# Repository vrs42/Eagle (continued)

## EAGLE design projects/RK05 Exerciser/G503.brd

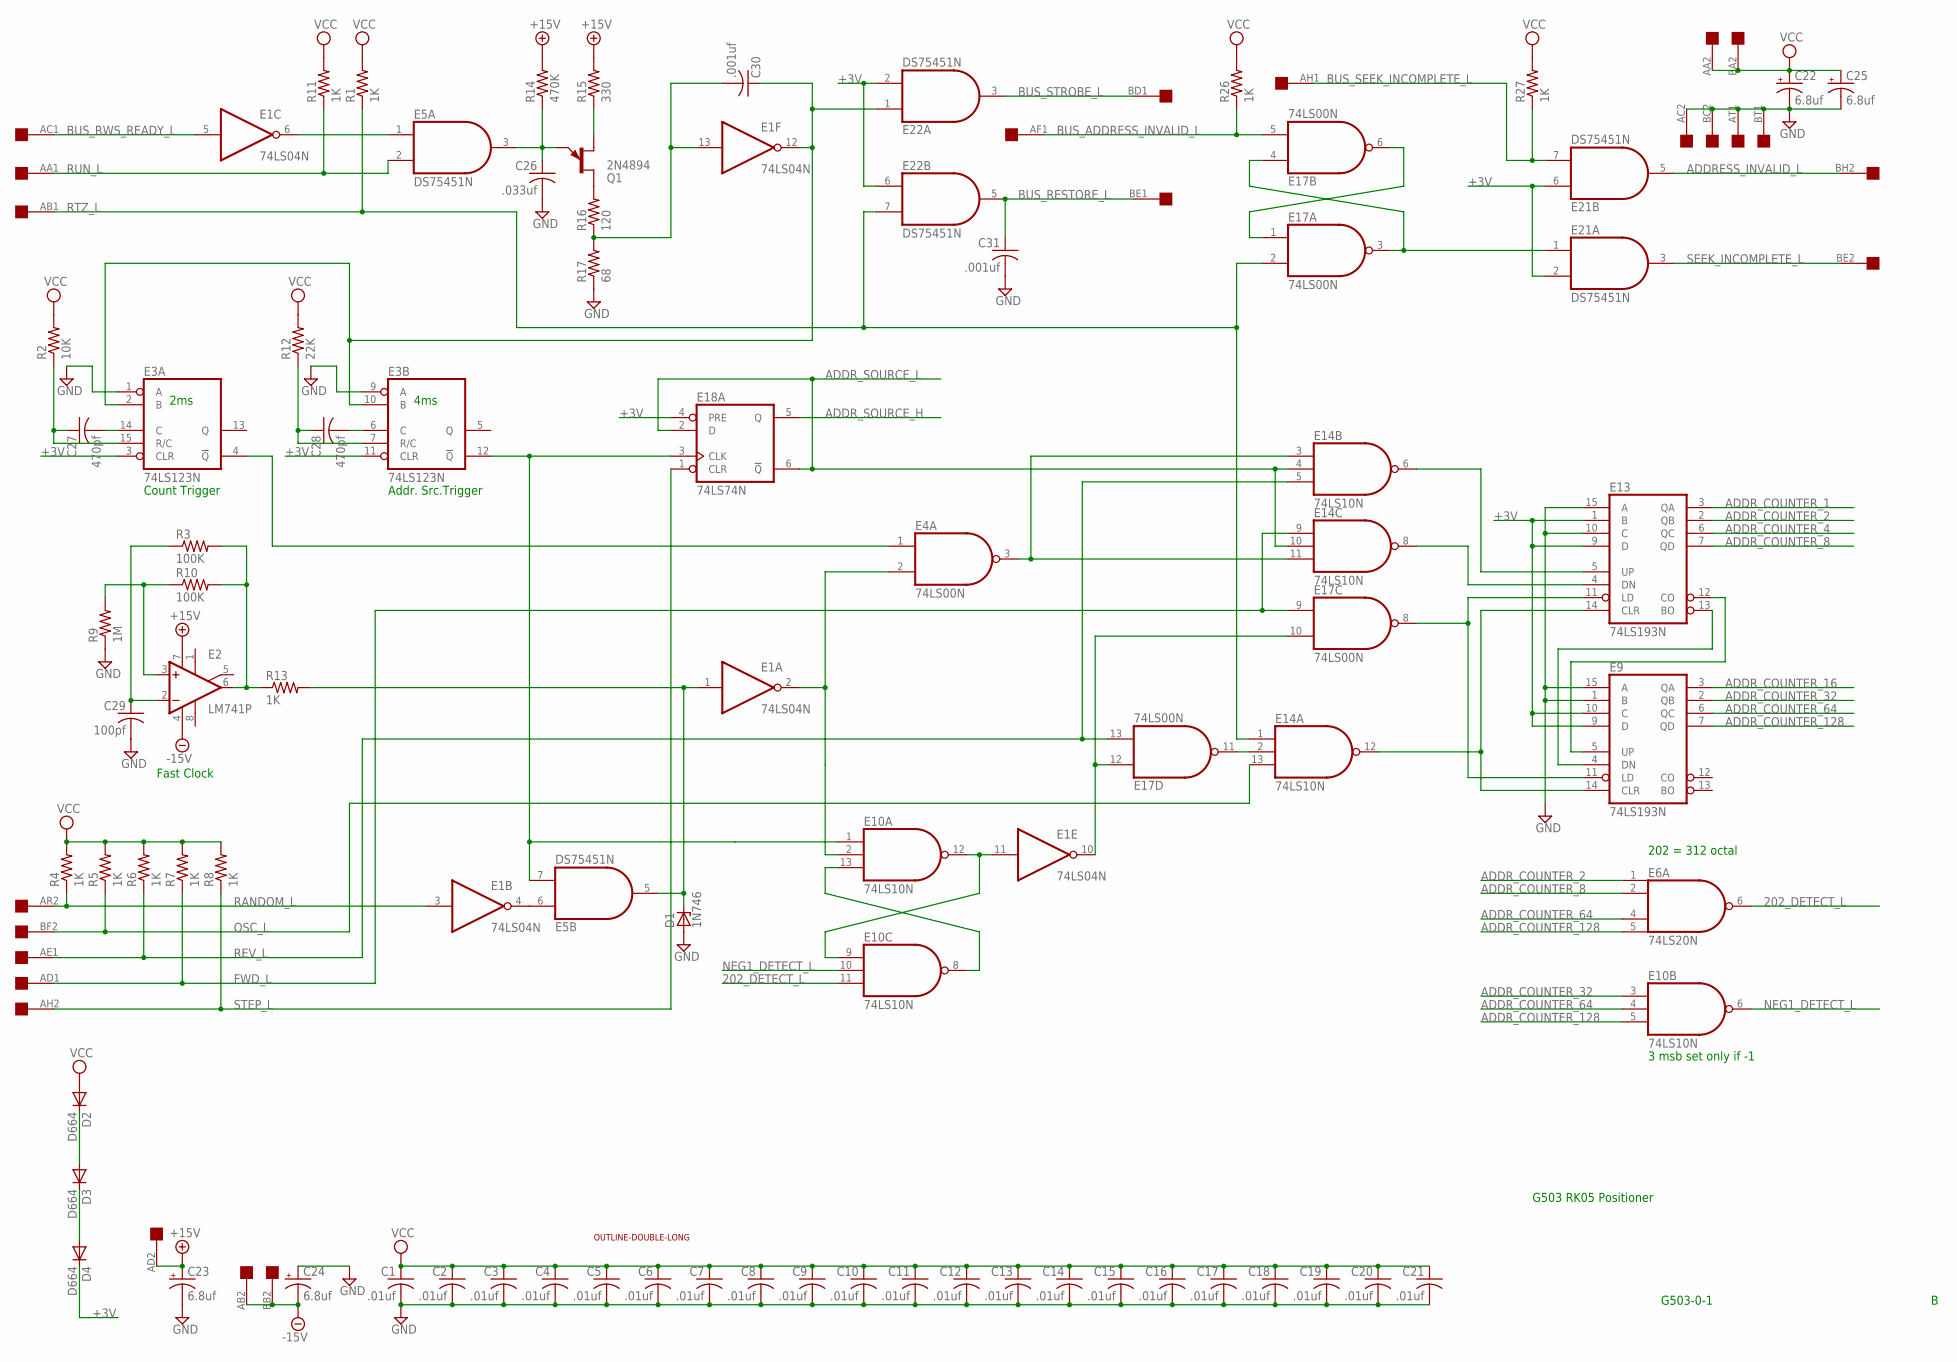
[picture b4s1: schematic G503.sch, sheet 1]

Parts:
AB03: DOUBLE; EDGE-CON4
C1, C2, C3, C4, C5, C6, C7, C8, C9, C10, C11, C12, C13, C14, C15, C16, C17, C18, C19, C20, C21: .01uf; C075-032X103
C22, C23, C24, C25: 6.8uf; E25-9
C26: .033uf; C075-032X103
C27, C28: 470pf; C075-032X103
C29: 100pf; C075-032X103
C30, C31: .001uf; C075-032X103
D1: 1N746; DO35Z10
D2, D3, D4: D664; DO35-10
E1: 74LS04N; DIL14
E2: LM741P; DIL08
E3: 74LS123N; DIL16
E4, E17: 74LS00N; DIL14
E5, E21, E22: DS75451N; DIL08
E6: 74LS20N; DIL14
E9, E13: 74LS193N; DIL16
E10, E14: 74LS10N; DIL14
E18: 74LS74N; DIL14
Q1: 2N4894; TO92E
R1, R4, R5, R6, R7, R8, R11, R13, R26, R27: 1K; 0207/10
R2: 10K; 0207/10
R3, R10: 100K; 0207/10
R9: 1M; 0207/10
R12: 22K; 0207/10
R14: 470K; 0207/10
R15: 330; 0207/10
R16: 120; 0207/10
R17: 68; 0207/10
U$1: OUTLINE-DOUBLE-LONG; DOUBLE-LONG

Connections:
202_DETECT_L: E6.6 (O), E10.11 (I2)
+3V: D4.C, E3.3 (CLR), E3.11 (CLR), E9.9 (D), E9.10 (C), E13.1 (B), E13.9 (D), E18.4 (PRE), E21.2 (I1), E21.6 (I0), E22.2 (I1), E22.6 (I0)
+15V: AB03.AD2, C23.+, E2.7 (V+), R14.2, R15.2
-15V: AB03.AB2, AB03.BB2, C24.-, E2.4 (V-)
ADDRESS_INVALID_L: AB03.BH2, E21.5 (O)
ADDR_COUNTER_1: E13.3 (QA); also elsewhere on the board
ADDR_COUNTER_2: E6.1 (I0), E13.2 (QB); also elsewhere on the board
ADDR_COUNTER_4: E13.6 (QC); also elsewhere on the board
ADDR_COUNTER_8: E6.2 (I1), E13.7 (QD); also elsewhere on the board
ADDR_COUNTER_16: E9.3 (QA); also elsewhere on the board
ADDR_COUNTER_32: E9.2 (QB), E10.3 (I0); also elsewhere on the board
ADDR_COUNTER_64: E6.4 (I2), E9.6 (QC), E10.4 (I1); also elsewhere on the board
ADDR_COUNTER_128: E6.5 (I3), E9.7 (QD), E10.5 (I2); also elsewhere on the board
ADDR_SOURCE_H: E18.5 (Q); also elsewhere on the board
ADDR_SOURCE_L: E14.4 (I1), E14.10 (I1), E18.2 (D), E18.6 (!Q); also elsewhere on the board
BUS_ADDRESS_INVALID_L: AB03.AF1, E17.5 (I1), R26.1
BUS_RESTORE_L: AB03.BE1, C31.1, E22.5 (O)
BUS_RWS_READY_L: AB03.AC1, E1.5 (I)
BUS_SEEK_INCOMPLETE_L: AB03.AH1, E21.7 (I1), R27.1
BUS_STROBE_L: AB03.BD1, E22.3 (O)
FWD_L: AB03.AD1, E14.9 (I0), E17.9 (I0), R7.1
GND: AB03.AC2, AB03.AT1, AB03.BC2, AB03.BT1, C1.2, C2.2, C3.2, C4.2, C5.2, C6.2, C7.2, C8.2, C9.2, C10.2, C11.2, C12.2, C13.2, C14.2, C15.2, C16.2, C17.2, C18.2, C19.2, C20.2, C21.2, C22.-, C23.-, C24.+, C25.-, C26.2, C29.2, C31.2, D1.A, E1.7 (GND), E3.1 (A), E3.8 (GND), E3.9 (A), E4.7 (GND), E5.4 (GND), E6.7 (GND), E9.1 (B), E9.8 (GND), E9.15 (A), E10.7 (GND), E13.8 (GND), E13.10 (C), E13.15 (A), E14.7 (GND), E17.7 (GND), E18.7 (GND), E21.4 (GND), E22.4 (GND), R9.1, R17.1; also elsewhere on the board
unnamed: E1.6 (O), E5.1 (I0)
unnamed: C26.1, E5.3 (O), Q1.E, R14.1
unnamed: Q1.B1, R15.1
unnamed: Q1.B2, R16.2
unnamed: C30.2, E1.13 (I), R16.1, R17.2
unnamed: C30.1, E1.12 (O), E3.2 (B), E3.10 (B), E22.1 (I0)
unnamed: E17.1 (I0), E17.6 (O)
unnamed: E17.3 (O), E17.4 (I0), E21.1 (I0)
unnamed: C27.1, E3.15 (R/C), R2.1
unnamed: C27.2, E3.14 (C)
unnamed: C28.1, E3.7 (R/C), R12.1
unnamed: C28.2, E3.6 (C)
unnamed: E13.5 (UP), E14.6 (O)
unnamed: E9.4 (DN), E13.13 (BO)
unnamed: E9.5 (UP), E13.12 (CO)
unnamed: E13.4 (DN), E14.8 (O)
unnamed: E9.11 (LD), E13.11 (LD), E17.8 (O)
unnamed: E9.14 (CLR), E13.14 (CLR), E14.12 (O)
unnamed: C29.1, E2.2 (-IN), R3.1
unnamed: E2.6 (OUT), R3.2, R10.2, R13.1
unnamed: E2.3 (+IN), R9.2, R10.1
unnamed: D1.C, E1.1 (I), E5.5 (O), R13.2
unnamed: E1.2 (O), E4.2 (I1), E10.2 (I1)
unnamed: E3.4 (!Q), E4.1 (I0)
unnamed: D2.C, D3.A
unnamed: D3.C, D4.A
unnamed: E1.4 (O), E5.6 (I0)
unnamed: E10.8 (O), E10.13 (I2)
unnamed: E3.12 (!Q), E5.7 (I1), E10.1 (I0), E18.3 (CLK)
unnamed: E4.3 (O), E14.3 (I0), E14.11 (I2)
unnamed: E1.11 (I), E10.9 (I0), E10.12 (O)
unnamed: E14.2 (I1), E17.11 (O)
unnamed: E1.10 (O), E17.10 (I1), E17.12 (I0)
NEG1_DETECT_L: E10.6 (O), E10.10 (I1)
OSC_L: AB03.BF2, E14.13 (I2), R5.1
RANDOM_L: AB03.AR2, E1.3 (I), R4.1
REV_L: AB03.AE1, E14.5 (I2), E17.13 (I1), R6.1
RTZ_L: AB03.AB1, E14.1 (I0), E17.2 (I1), E22.7 (I1), R1.1
RUN_L: AB03.AA1, E5.2 (I1), R11.1
SEEK_INCOMPLETE_L: AB03.BE2, E21.3 (O)
STEP_L: AB03.AH2, E18.1 (CLR), R8.1
VCC: AB03.AA2, AB03.BA2, C1.1, C2.1, C3.1, C4.1, C5.1, C6.1, C7.1, C8.1, C9.1, C10.1, C11.1, C12.1, C13.1, C14.1, C15.1, C16.1, C17.1, C18.1, C19.1, C20.1, C21.1, C22.+, C25.+, D2.A, E1.14 (VCC), E3.16 (VCC), E4.14 (VCC), E5.8 (VCC), E6.14 (VCC), E9.16 (VCC), E10.14 (VCC), E13.16 (VCC), E14.14 (VCC), E17.14 (VCC), E18.14 (VCC), E21.8 (VCC), E22.8 (VCC), R1.2, R2.2, R4.2, R5.2, R6.2, R7.2, R8.2, R11.2, R12.2, R26.2, R27.2; also elsewhere on the board

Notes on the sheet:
2ms
4ms
Count Trigger
Addr. Src.Trigger
202 = 312 octal
3 msb set only if -1
Fast Clock
G503 RK05 Positioner
G503-0-1

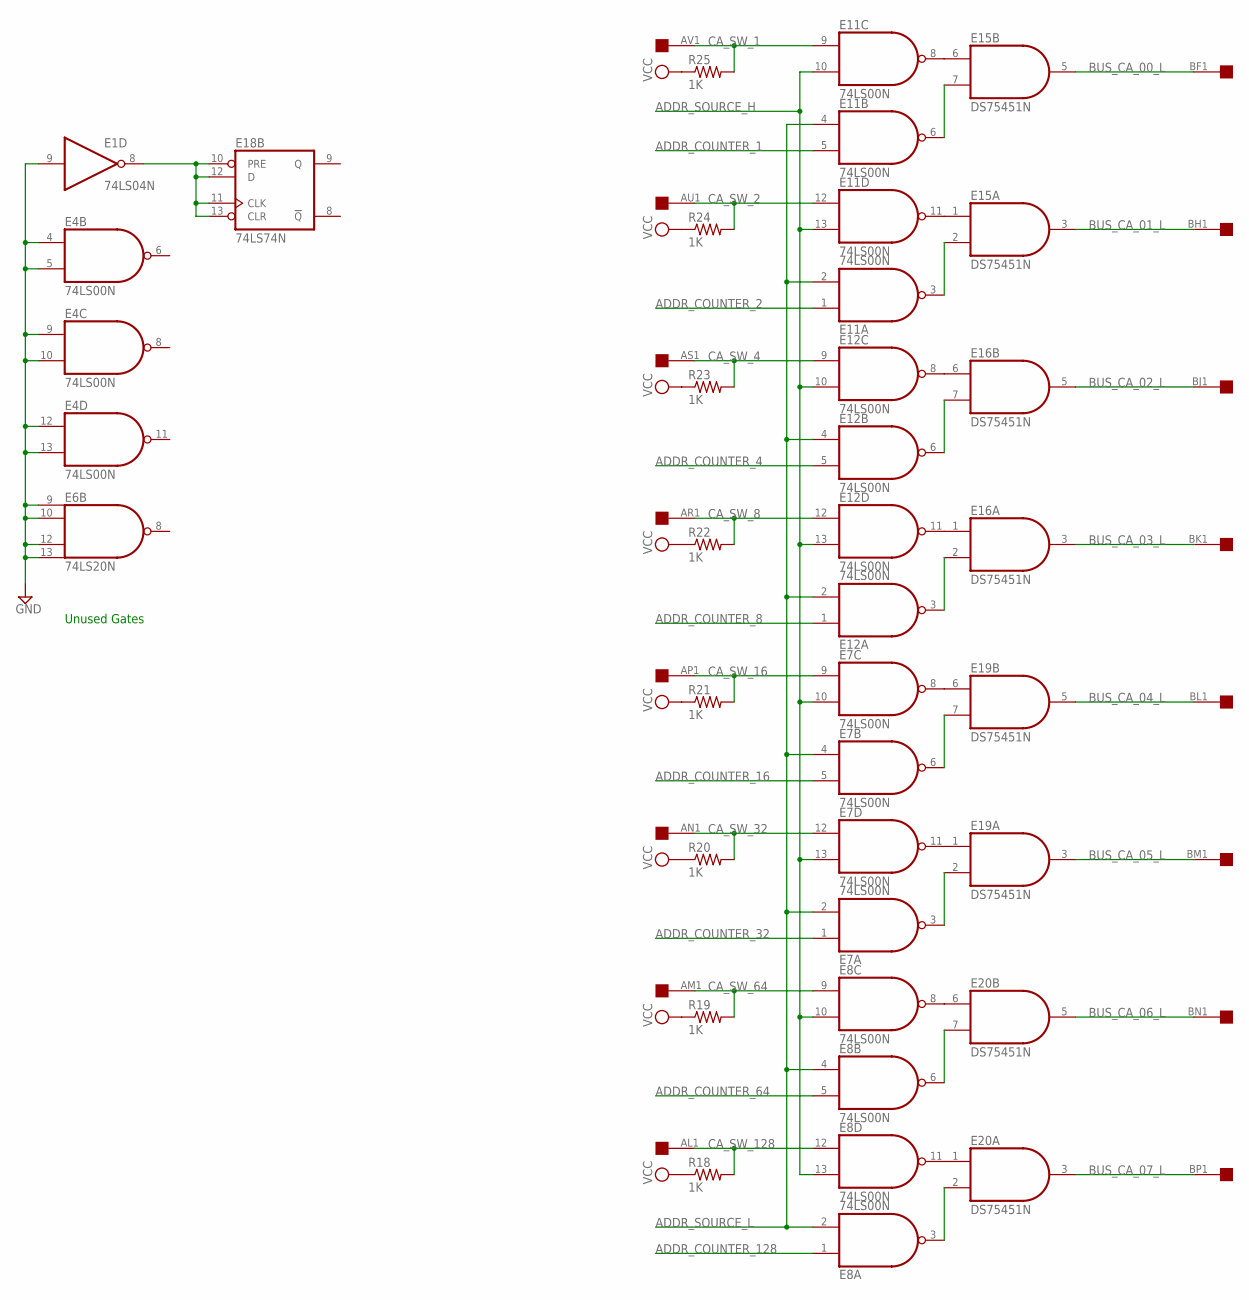
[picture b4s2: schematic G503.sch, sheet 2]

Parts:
AB03: DOUBLE; EDGE-CON4
E1: 74LS04N; DIL14
E4, E7, E8, E11, E12: 74LS00N; DIL14
E6: 74LS20N; DIL14
E15, E16, E19, E20: DS75451N; DIL08
E18: 74LS74N; DIL14
R18, R19, R20, R21, R22, R23, R24, R25: 1K; 0207/10

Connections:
ADDR_COUNTER_1: E11.5 (I1); also elsewhere on the board
ADDR_COUNTER_2: E11.1 (I0); also elsewhere on the board
ADDR_COUNTER_4: E12.5 (I1); also elsewhere on the board
ADDR_COUNTER_8: E12.1 (I0); also elsewhere on the board
ADDR_COUNTER_16: E7.5 (I1); also elsewhere on the board
ADDR_COUNTER_32: E7.1 (I0); also elsewhere on the board
ADDR_COUNTER_64: E8.5 (I1); also elsewhere on the board
ADDR_COUNTER_128: E8.1 (I0); also elsewhere on the board
ADDR_SOURCE_H: E7.10 (I1), E7.13 (I1), E8.10 (I1), E8.13 (I1), E11.10 (I1), E11.13 (I1), E12.10 (I1), E12.13 (I1); also elsewhere on the board
ADDR_SOURCE_L: E7.2 (I1), E7.4 (I0), E8.2 (I1), E8.4 (I0), E11.2 (I1), E11.4 (I0), E12.2 (I1), E12.4 (I0); also elsewhere on the board
BUS_CA_00_L: AB03.BF1, E15.5 (O)
BUS_CA_01_L: AB03.BH1, E15.3 (O)
BUS_CA_02_L: AB03.BJ1, E16.5 (O)
BUS_CA_03_L: AB03.BK1, E16.3 (O)
BUS_CA_04_L: AB03.BL1, E19.5 (O)
BUS_CA_05_L: AB03.BM1, E19.3 (O)
BUS_CA_06_L: AB03.BN1, E20.5 (O)
BUS_CA_07_L: AB03.BP1, E20.3 (O)
CA_SW_1: AB03.AV1, E11.9 (I0), R25.2
CA_SW_2: AB03.AU1, E11.12 (I0), R24.2
CA_SW_4: AB03.AS1, E12.9 (I0), R23.2
CA_SW_8: AB03.AR1, E12.12 (I0), R22.2
CA_SW_16: AB03.AP1, E7.9 (I0), R21.2
CA_SW_32: AB03.AN1, E7.12 (I0), R20.2
CA_SW_64: AB03.AM1, E8.9 (I0), R19.2
CA_SW_128: AB03.AL1, E8.12 (I0), R18.2
GND: E1.7 (GND), E1.9 (I), E4.4 (I0), E4.5 (I1), E4.7 (GND), E4.9 (I0), E4.10 (I1), E4.12 (I0), E4.13 (I1), E6.7 (GND), E6.9 (I0), E6.10 (I1), E6.12 (I2), E6.13 (I3), E7.7 (GND), E8.7 (GND), E11.7 (GND), E12.7 (GND), E15.4 (GND), E16.4 (GND), E18.7 (GND), E19.4 (GND), E20.4 (GND); also elsewhere on the board
unnamed: E11.6 (O), E15.7 (I1)
unnamed: E11.8 (O), E15.6 (I0)
unnamed: E11.3 (O), E15.2 (I1)
unnamed: E11.11 (O), E15.1 (I0)
unnamed: E12.8 (O), E16.6 (I0)
unnamed: E12.6 (O), E16.7 (I1)
unnamed: E12.11 (O), E16.1 (I0)
unnamed: E12.3 (O), E16.2 (I1)
unnamed: E7.6 (O), E19.7 (I1)
unnamed: E7.3 (O), E19.2 (I1)
unnamed: E8.6 (O), E20.7 (I1)
unnamed: E8.3 (O), E20.2 (I1)
unnamed: E8.11 (O), E20.1 (I0)
unnamed: E8.8 (O), E20.6 (I0)
unnamed: E7.11 (O), E19.1 (I0)
unnamed: E7.8 (O), E19.6 (I0)
unnamed: E1.8 (O), E18.10 (PRE), E18.11 (CLK), E18.12 (D), E18.13 (CLR)
VCC: E1.14 (VCC), E4.14 (VCC), E6.14 (VCC), E7.14 (VCC), E8.14 (VCC), E11.14 (VCC), E12.14 (VCC), E15.8 (VCC), E16.8 (VCC), E18.14 (VCC), E19.8 (VCC), E20.8 (VCC), R18.1, R19.1, R20.1, R21.1, R22.1, R23.1, R24.1, R25.1; also elsewhere on the board

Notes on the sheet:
Unused Gates

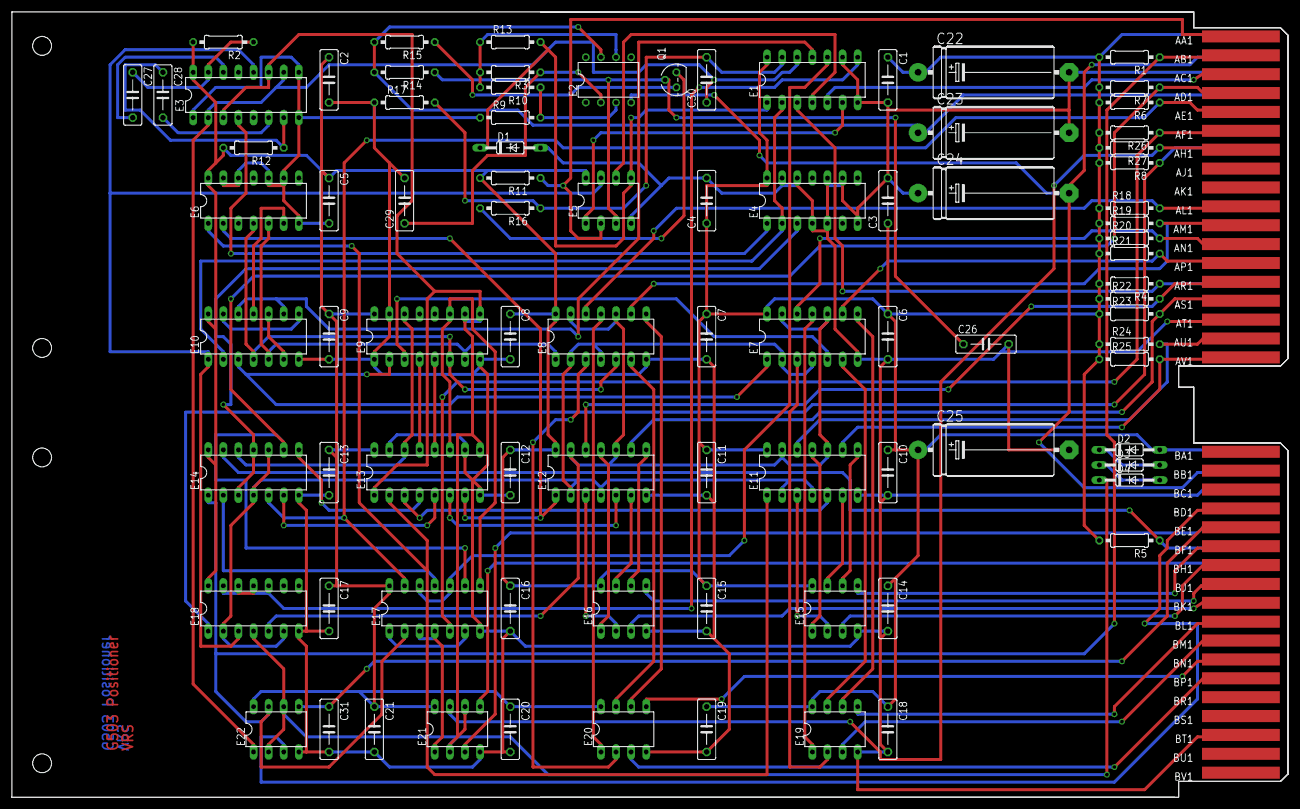
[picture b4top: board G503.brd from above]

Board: 2 copper layers, 214.6 x 132.1 mm, 87 parts (0 on the bottom side), 97 nets.

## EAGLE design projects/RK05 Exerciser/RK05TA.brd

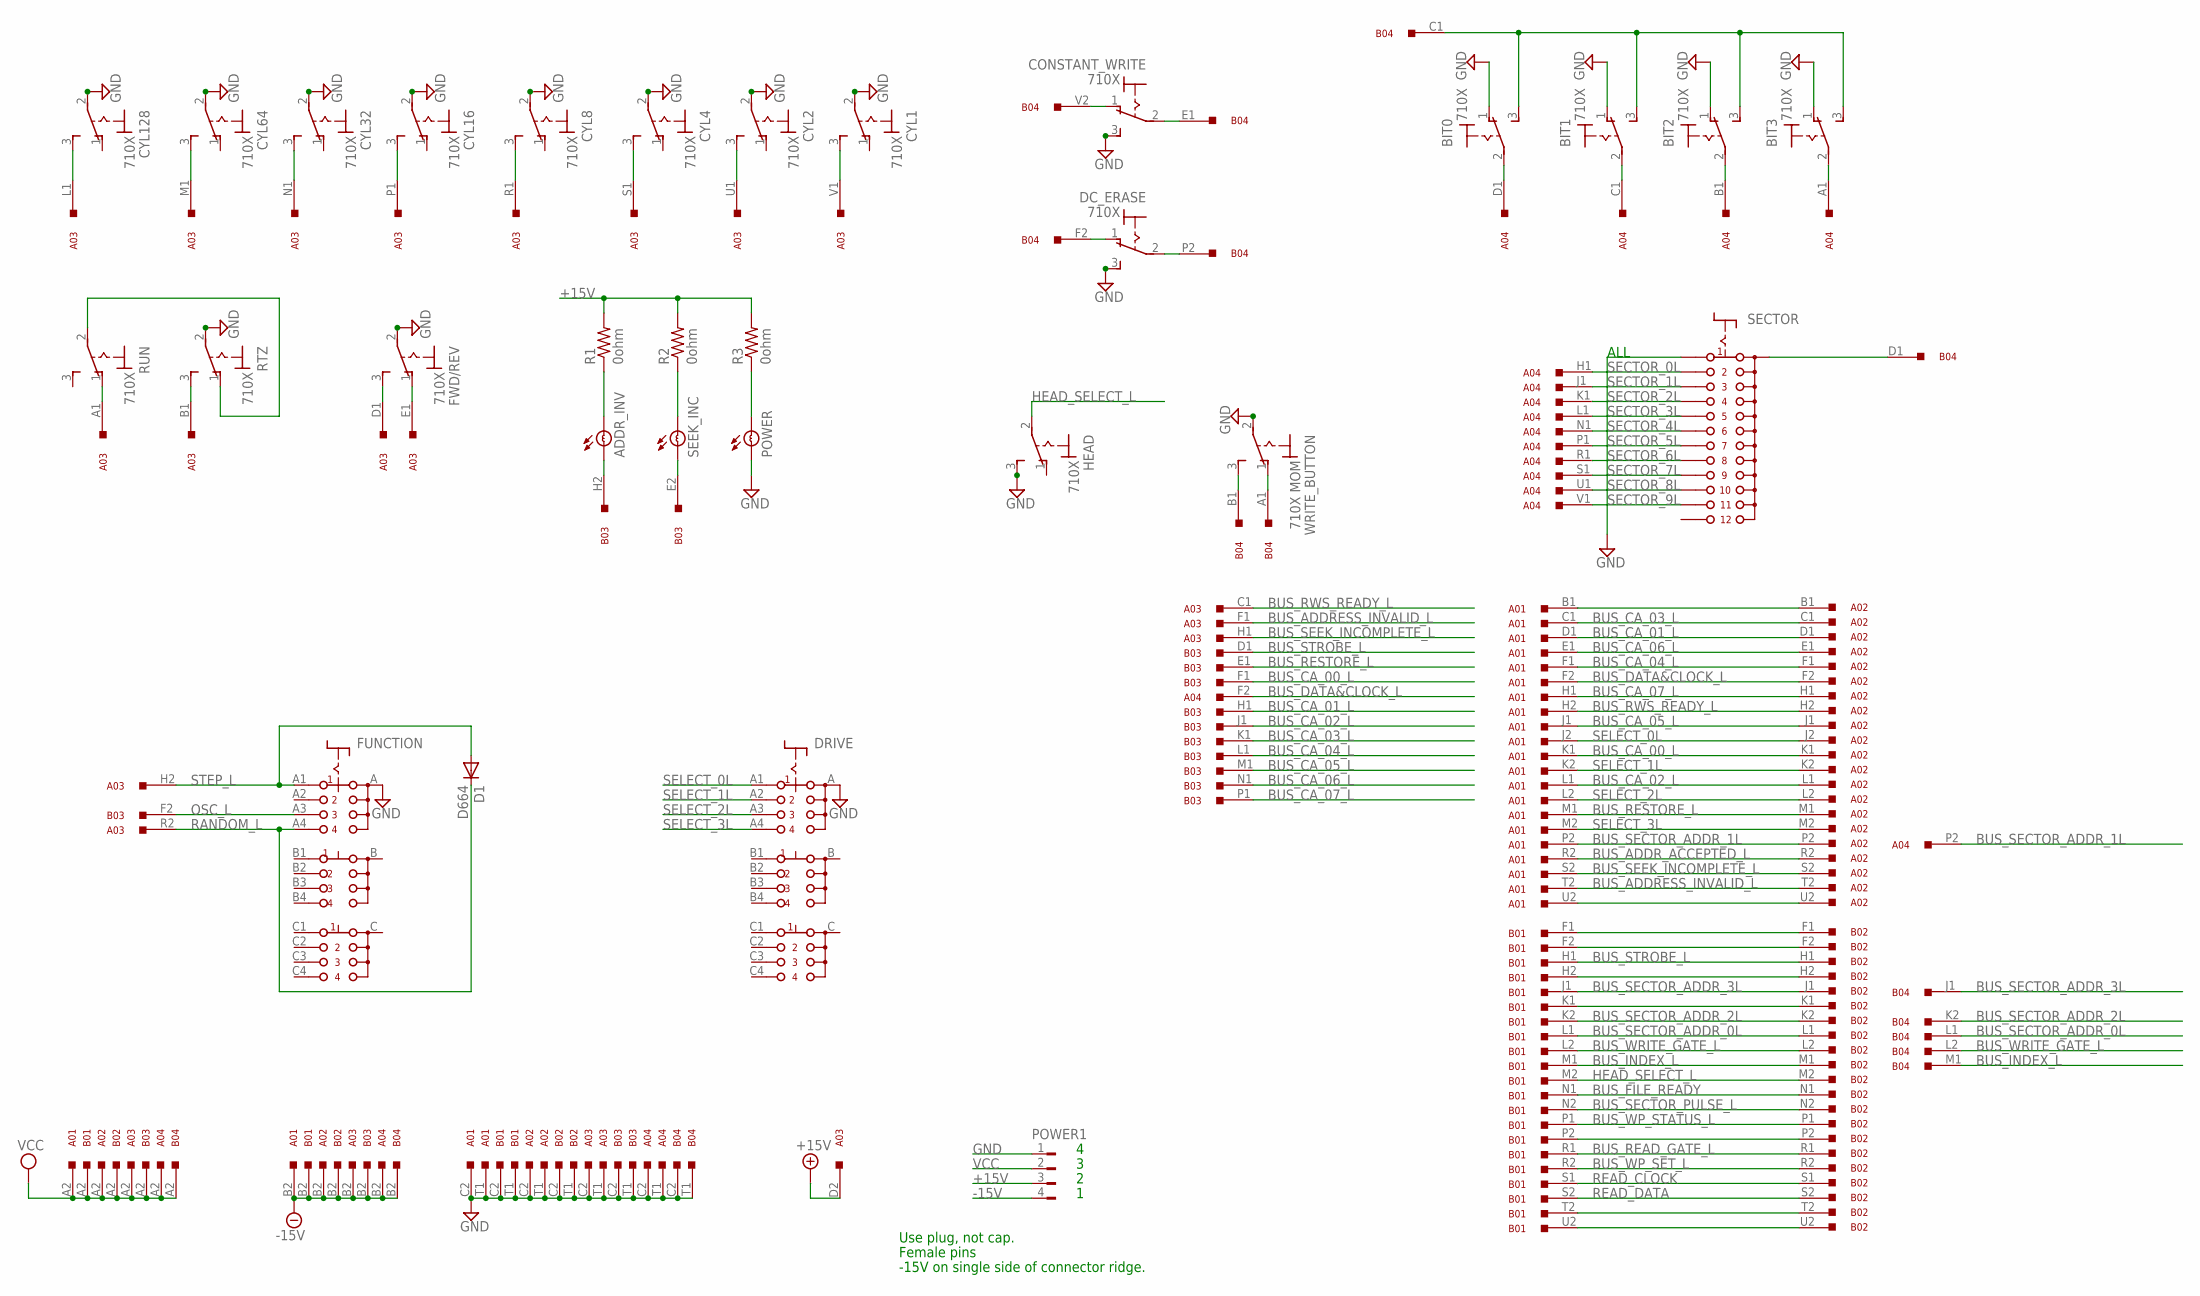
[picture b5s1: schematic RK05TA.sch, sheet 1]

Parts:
A01: BC11A; H807
A02: M930; H807
A03: G503; H807
A04: G502; H807
ADDR_INV: BULB
B01: BC11A; H807
B02: M930; H807
B03: G503; H807
B04: G502; H807
BIT0, BIT1, BIT2, BIT3: 710X; 7109MD9V3
CONSTANT_WRITE: 710X; 7109MD9V3
CYL1, CYL2, CYL4, CYL8, CYL16, CYL32, CYL64, CYL128: 710X; 7109MD9V3
D1: D664; DO35-10
DC_ERASE: 710X; 7109MD9V3
DRIVE: CK103X04
FUNCTION: CK103X04
FWD/REV: 710X; 7109MD9V3
HEAD: 710X; 7109MD9V3
POWER: BULB
POWER1: FLOPPY-4
R1, R2, R3: 0ohm; 0207/10
RTZ: 710X; 7109MD9V3
RUN: 710X; 7109MD9V3
SECTOR: CK101X12
SEEK_INC: BULB
WRITE_BUTTON: 710X MOM; 7109MD9V3

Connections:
+3VA: B04.F2, DC_ERASE.1 (O); also elsewhere on the board
+3VC: B04.V2, CONSTANT_WRITE.1 (O); also elsewhere on the board
+15V: A03.D2, POWER1.3, R1.2, R2.2, R3.2; also elsewhere on the board
-15V: A01.B2, A02.B2, A03.B2, A04.B2, B01.B2, B02.B2, B03.B2, B04.B2, POWER1.4; also elsewhere on the board
ADDRESS_INVALID_L: ADDR_INV.B, B03.H2; also elsewhere on the board
BIT_0L: A04.D1, BIT0.2; also elsewhere on the board
BIT_1L: A04.C1, BIT1.2; also elsewhere on the board
BIT_2L: A04.B1, BIT2.2; also elsewhere on the board
BIT_3L: A04.A1, BIT3.2; also elsewhere on the board
BUS_ADDRESS_INVALID_L: A01.T2, A02.T2, A03.F1
BUS_ADDR_ACCEPTED_L: A01.R2, A02.R2
BUS_CA_00_L: A01.K1, A02.K1, B03.F1
BUS_CA_01_L: A01.D1, A02.D1, B03.H1
BUS_CA_02_L: A01.L1, A02.L1, B03.J1
BUS_CA_03_L: A01.C1, A02.C1, B03.K1
BUS_CA_04_L: A01.F1, A02.F1, B03.L1
BUS_CA_05_L: A01.J1, A02.J1, B03.M1
BUS_CA_06_L: A01.E1, A02.E1, B03.N1
BUS_CA_07_L: A01.H1, A02.H1, B03.P1
BUS_DATA&CLOCK_L: A01.F2, A02.F2, A04.F2
BUS_FILE_READY: B01.N1, B02.N1
BUS_INDEX_L: B01.M1, B02.M1, B04.M1
BUS_READ_GATE_L: B01.R1, B02.R1
BUS_RESTORE_L: A01.M1, A02.M1, B03.E1
BUS_RWS_READY_L: A01.H2, A02.H2, A03.C1
BUS_SECTOR_ADDR_0L: B01.L1, B02.L1, B04.L1
BUS_SECTOR_ADDR_1L: A01.P2, A02.P2, A04.P2
BUS_SECTOR_ADDR_2L: B01.K2, B02.K2, B04.K2
BUS_SECTOR_ADDR_3L: B01.J1, B02.J1, B04.J1
BUS_SECTOR_PULSE_L: B01.N2, B02.N2
BUS_SEEK_INCOMPLETE_L: A01.S2, A02.S2, A03.H1
BUS_STROBE_L: B01.H1, B02.H1, B03.D1
BUS_WP_SET_L: B01.R2, B02.R2
BUS_WP_STATUS_L: B01.P1, B02.P1
BUS_WRITE_GATE_L: B01.L2, B02.L2, B04.L2
CA_SW_1: A03.V1, CYL1.3 (S); also elsewhere on the board
CA_SW_2: A03.U1, CYL2.3 (S); also elsewhere on the board
CA_SW_4: A03.S1, CYL4.3 (S); also elsewhere on the board
CA_SW_8: A03.R1, CYL8.3 (S); also elsewhere on the board
CA_SW_16: A03.P1, CYL16.3 (S); also elsewhere on the board
CA_SW_32: A03.N1, CYL32.3 (S); also elsewhere on the board
CA_SW_64: A03.M1, CYL64.3 (S); also elsewhere on the board
CA_SW_128: A03.L1, CYL128.3 (S); also elsewhere on the board
CONSTANT_WRITE_L: B04.E1, CONSTANT_WRITE.2; also elsewhere on the board
DATA_BITS: B04.C1, BIT0.3 (S), BIT1.3 (S), BIT2.3 (S), BIT3.3 (S); also elsewhere on the board
DC_ERASE: B04.P2, DC_ERASE.2; also elsewhere on the board
FWD_L: A03.D1, FWD/REV.3 (S); also elsewhere on the board
GND: A01.C2, A01.T1, A02.C2, A02.T1, A03.C2, A03.T1, A04.C2, A04.T1, B01.C2, B01.T1, B02.C2, B02.T1, B03.C2, B03.T1, B04.C2, B04.T1, BIT0.1 (O), BIT0.NC@1 (GND), BIT0.NC@2 (GND), BIT0.NC@3 (GND), BIT0.NC@4 (GND), BIT0.NC@5 (GND), BIT0.NC@6 (GND), BIT0.NC@7 (GND), BIT0.NC@8 (GND), BIT1.1 (O), BIT1.NC@1 (GND), BIT1.NC@2 (GND), BIT1.NC@3 (GND), BIT1.NC@4 (GND), BIT1.NC@5 (GND), BIT1.NC@6 (GND), BIT1.NC@7 (GND), BIT1.NC@8 (GND), BIT2.1 (O), BIT2.NC@1 (GND), BIT2.NC@2 (GND), BIT2.NC@3 (GND), BIT2.NC@4 (GND), BIT2.NC@5 (GND), BIT2.NC@6 (GND), BIT2.NC@7 (GND), BIT2.NC@8 (GND), BIT3.1 (O), BIT3.NC@1 (GND), BIT3.NC@2 (GND), BIT3.NC@3 (GND), BIT3.NC@4 (GND), BIT3.NC@5 (GND), BIT3.NC@6 (GND), BIT3.NC@7 (GND), BIT3.NC@8 (GND), CONSTANT_WRITE.3 (S), CONSTANT_WRITE.NC@1 (GND), CONSTANT_WRITE.NC@2 (GND), CONSTANT_WRITE.NC@3 (GND), CONSTANT_WRITE.NC@4 (GND), CONSTANT_WRITE.NC@5 (GND), CONSTANT_WRITE.NC@6 (GND), CONSTANT_WRITE.NC@7 (GND), CONSTANT_WRITE.NC@8 (GND), CYL1.2, CYL1.NC@1 (GND), CYL1.NC@2 (GND), CYL1.NC@3 (GND), CYL1.NC@4 (GND), CYL1.NC@5 (GND), CYL1.NC@6 (GND), CYL1.NC@7 (GND), CYL1.NC@8 (GND), CYL2.2, CYL2.NC@1 (GND), CYL2.NC@2 (GND), CYL2.NC@3 (GND), CYL2.NC@4 (GND), CYL2.NC@5 (GND), CYL2.NC@6 (GND), CYL2.NC@7 (GND), CYL2.NC@8 (GND), CYL4.2, CYL4.NC@1 (GND), CYL4.NC@2 (GND), CYL4.NC@3 (GND), CYL4.NC@4 (GND), CYL4.NC@5 (GND), CYL4.NC@6 (GND), CYL4.NC@7 (GND), CYL4.NC@8 (GND), CYL8.2, CYL8.NC@1 (GND), CYL8.NC@2 (GND), CYL8.NC@3 (GND), CYL8.NC@4 (GND), CYL8.NC@5 (GND), CYL8.NC@6 (GND), CYL8.NC@7 (GND), CYL8.NC@8 (GND), CYL16.2, CYL16.NC@1 (GND), CYL16.NC@2 (GND), CYL16.NC@3 (GND), CYL16.NC@4 (GND), CYL16.NC@5 (GND), CYL16.NC@6 (GND), CYL16.NC@7 (GND), CYL16.NC@8 (GND), CYL32.2, CYL32.NC@1 (GND), CYL32.NC@2 (GND), CYL32.NC@3 (GND), CYL32.NC@4 (GND), CYL32.NC@5 (GND), CYL32.NC@6 (GND), CYL32.NC@7 (GND), CYL32.NC@8 (GND), CYL64.2, CYL64.NC@1 (GND), CYL64.NC@2 (GND), CYL64.NC@3 (GND), CYL64.NC@4 (GND), CYL64.NC@5 (GND), CYL64.NC@6 (GND), CYL64.NC@7 (GND), CYL64.NC@8 (GND), CYL128.2, CYL128.NC@1 (GND), CYL128.NC@2 (GND), CYL128.NC@3 (GND), CYL128.NC@4 (GND), CYL128.NC@5 (GND), CYL128.NC@6 (GND), CYL128.NC@7 (GND), CYL128.NC@8 (GND), DC_ERASE.3 (S), DC_ERASE.NC@1 (GND), DC_ERASE.NC@2 (GND), DC_ERASE.NC@3 (GND), DC_ERASE.NC@4 (GND), DC_ERASE.NC@5 (GND), DC_ERASE.NC@6 (GND), DC_ERASE.NC@7 (GND), DC_ERASE.NC@8 (GND), DRIVE.A, FUNCTION.A, FWD/REV.2, FWD/REV.NC@1 (GND), FWD/REV.NC@2 (GND), FWD/REV.NC@3 (GND), FWD/REV.NC@4 (GND), FWD/REV.NC@5 (GND), FWD/REV.NC@6 (GND), FWD/REV.NC@7 (GND), FWD/REV.NC@8 (GND), HEAD.3 (S), HEAD.NC@1 (GND), HEAD.NC@2 (GND), HEAD.NC@3 (GND), HEAD.NC@4 (GND), HEAD.NC@5 (GND), HEAD.NC@6 (GND), HEAD.NC@7 (GND), HEAD.NC@8 (GND), POWER.B, POWER1.1, RTZ.2, RTZ.NC@1 (GND), RTZ.NC@2 (GND), RTZ.NC@3 (GND), RTZ.NC@4 (GND), RTZ.NC@5 (GND), RTZ.NC@6 (GND), RTZ.NC@7 (GND), RTZ.NC@8 (GND), RUN.NC@1 (GND), RUN.NC@2 (GND), RUN.NC@3 (GND), RUN.NC@4 (GND), RUN.NC@5 (GND), RUN.NC@6 (GND), RUN.NC@7 (GND), RUN.NC@8 (GND), SECTOR.1, WRITE_BUTTON.2, WRITE_BUTTON.NC@1 (GND), WRITE_BUTTON.NC@2 (GND), WRITE_BUTTON.NC@3 (GND), WRITE_BUTTON.NC@4 (GND), WRITE_BUTTON.NC@5 (GND), WRITE_BUTTON.NC@6 (GND), WRITE_BUTTON.NC@7 (GND), WRITE_BUTTON.NC@8 (GND); also elsewhere on the board
HEAD_SELECT_L: B01.M2, B02.M2, HEAD.2; also elsewhere on the board
unnamed: RTZ.1 (O), RUN.2
unnamed: ADDR_INV.A, R1.1
unnamed: R2.1, SEEK_INC.A
unnamed: POWER.A, R3.1
unnamed: A01.U2, A02.U2
unnamed: B01.T2, B02.T2
unnamed: A01.B1, A02.B1
unnamed: B01.F1, B02.F1
unnamed: B01.F2, B02.F2
unnamed: B01.H2, B02.H2
unnamed: B01.K1, B02.K1
unnamed: B01.P2, B02.P2
unnamed: B01.U2, B02.U2
OSC_L: B03.F2, FUNCTION.A3; also elsewhere on the board
RANDOM_L: A03.R2, D1.C, FUNCTION.A4; also elsewhere on the board
READ_CLOCK: B01.S1, B02.S1
READ_DATA: B01.S2, B02.S2
REV_L: A03.E1, FWD/REV.1 (O); also elsewhere on the board
RTZ_L: A03.B1, RTZ.3 (S); also elsewhere on the board
RUN_L: A03.A1, RUN.1 (O); also elsewhere on the board
SECTOR_0L: A04.H1, SECTOR.2; also elsewhere on the board
SECTOR_1L: A04.J1, SECTOR.3; also elsewhere on the board
SECTOR_2L: A04.K1, SECTOR.4; also elsewhere on the board
SECTOR_3L: A04.L1, SECTOR.5; also elsewhere on the board
SECTOR_4L: A04.N1, SECTOR.6; also elsewhere on the board
SECTOR_5L: A04.P1, SECTOR.7; also elsewhere on the board
SECTOR_6L: A04.R1, SECTOR.8; also elsewhere on the board
SECTOR_7L: A04.S1, SECTOR.9; also elsewhere on the board
SECTOR_8L: A04.U1, SECTOR.10; also elsewhere on the board
SECTOR_9L: A04.V1, SECTOR.11; also elsewhere on the board
SECTOR_SELECT_L: B04.D1, SECTOR.A; also elsewhere on the board
SEEK_INCOMPLETE_L: B03.E2, SEEK_INC.B; also elsewhere on the board
SELECT_0L: A01.J2, A02.J2, DRIVE.A1; also elsewhere on the board
SELECT_1L: A01.K2, A02.K2, DRIVE.A2; also elsewhere on the board
SELECT_2L: A01.L2, A02.L2, DRIVE.A3; also elsewhere on the board
SELECT_3L: A01.M2, A02.M2, DRIVE.A4; also elsewhere on the board
STEP_L: A03.H2, D1.A, FUNCTION.A1; also elsewhere on the board
VCC: A01.A2, A02.A2, A03.A2, A04.A2, B01.A2, B02.A2, B03.A2, B04.A2, POWER1.2; also elsewhere on the board
WRITE_H: B04.A1, WRITE_BUTTON.1 (O); also elsewhere on the board
WRITE_L: B04.B1, WRITE_BUTTON.3 (S); also elsewhere on the board

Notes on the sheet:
ALL
Use plug, not cap.
Female pins
-15V on single side of connector ridge.

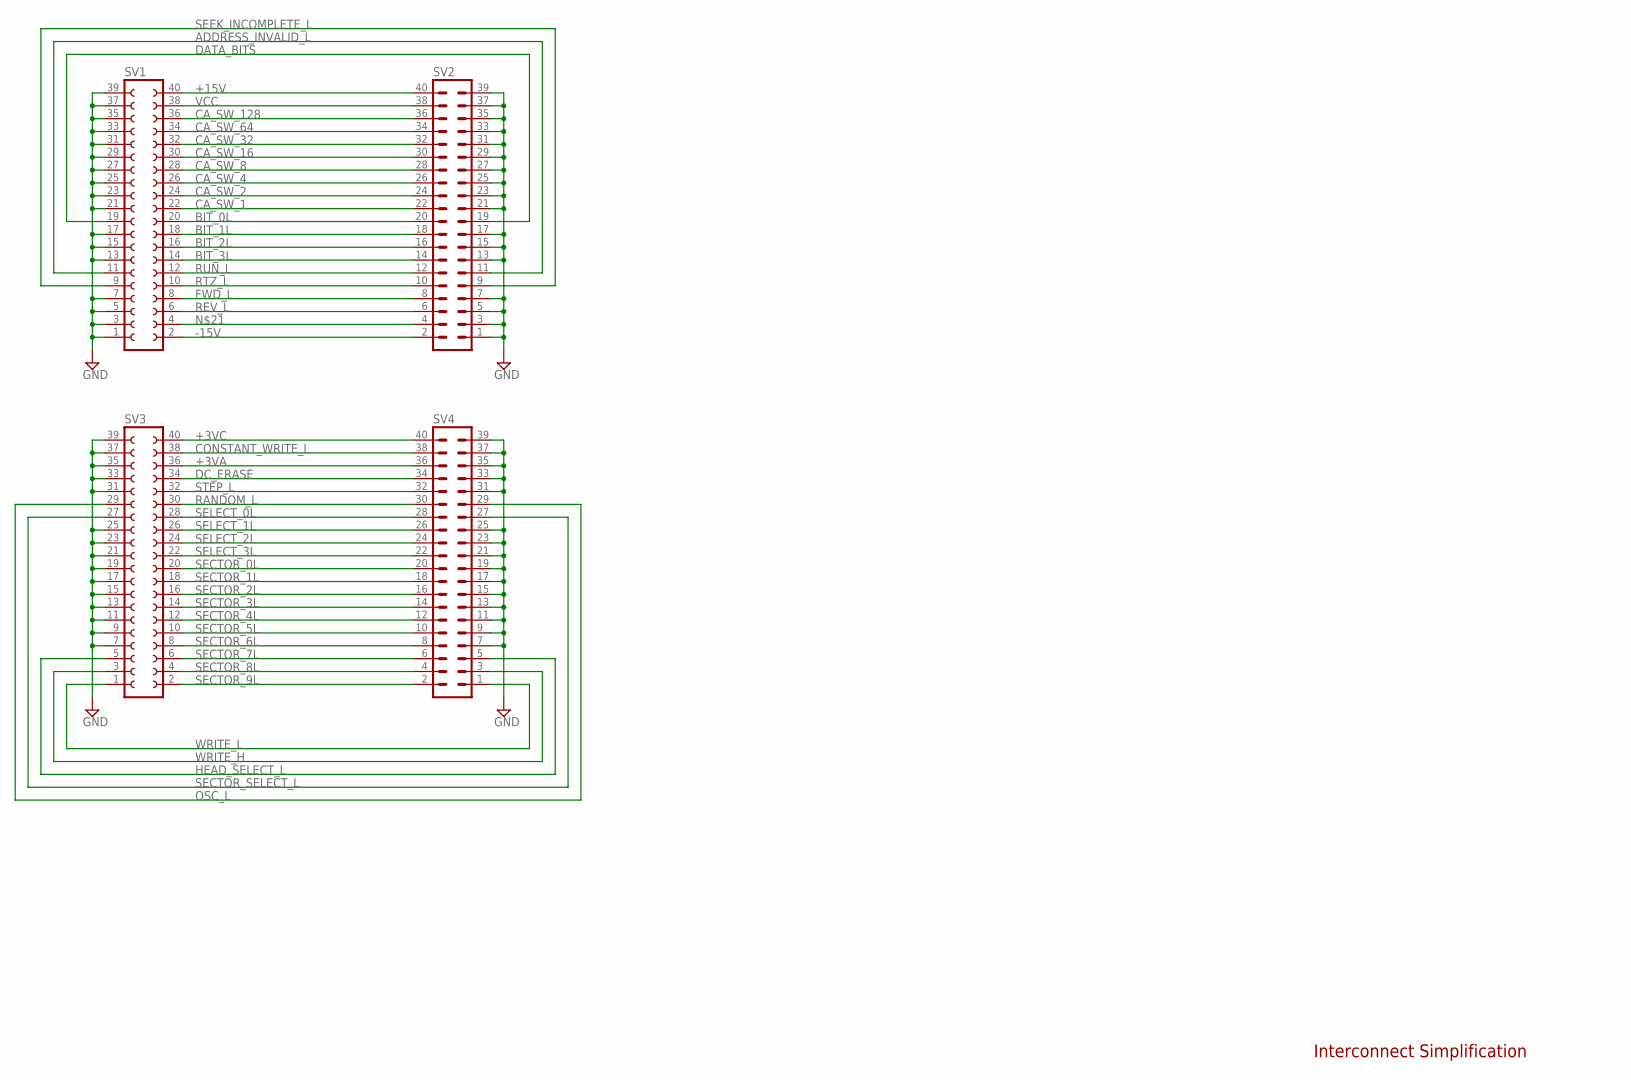
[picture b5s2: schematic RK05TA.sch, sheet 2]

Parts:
SV1, SV3: FE20-2W
SV2, SV4: MA20-2

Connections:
+3VA: SV3.36, SV4.36; also elsewhere on the board
+3VC: SV3.40, SV4.40; also elsewhere on the board
+15V: SV1.40, SV2.40; also elsewhere on the board
-15V: SV1.2, SV2.2; also elsewhere on the board
ADDRESS_INVALID_L: SV1.11, SV2.11; also elsewhere on the board
BIT_0L: SV1.20, SV2.20; also elsewhere on the board
BIT_1L: SV1.18, SV2.18; also elsewhere on the board
BIT_2L: SV1.16, SV2.16; also elsewhere on the board
BIT_3L: SV1.14, SV2.14; also elsewhere on the board
CA_SW_1: SV1.22, SV2.22; also elsewhere on the board
CA_SW_2: SV1.24, SV2.24; also elsewhere on the board
CA_SW_4: SV1.26, SV2.26; also elsewhere on the board
CA_SW_8: SV1.28, SV2.28; also elsewhere on the board
CA_SW_16: SV1.30, SV2.30; also elsewhere on the board
CA_SW_32: SV1.32, SV2.32; also elsewhere on the board
CA_SW_64: SV1.34, SV2.34; also elsewhere on the board
CA_SW_128: SV1.36, SV2.36; also elsewhere on the board
CONSTANT_WRITE_L: SV3.38, SV4.38; also elsewhere on the board
DATA_BITS: SV1.19, SV2.19; also elsewhere on the board
DC_ERASE: SV3.34, SV4.34; also elsewhere on the board
FWD_L: SV1.8, SV2.8; also elsewhere on the board
GND: SV1.1, SV1.3, SV1.5, SV1.7, SV1.13, SV1.15, SV1.17, SV1.21, SV1.23, SV1.25, SV1.27, SV1.29, SV1.31, SV1.33, SV1.35, SV1.37, SV1.39, SV2.1, SV2.3, SV2.5, SV2.7, SV2.13, SV2.15, SV2.17, SV2.21, SV2.23, SV2.25, SV2.27, SV2.29, SV2.31, SV2.33, SV2.35, SV2.37, SV2.39, SV3.7, SV3.9, SV3.11, SV3.13, SV3.15, SV3.17, SV3.19, SV3.21, SV3.23, SV3.25, SV3.31, SV3.33, SV3.35, SV3.37, SV3.39, SV4.7, SV4.9, SV4.11, SV4.13, SV4.15, SV4.17, SV4.19, SV4.21, SV4.23, SV4.25, SV4.31, SV4.33, SV4.35, SV4.37, SV4.39; also elsewhere on the board
HEAD_SELECT_L: SV3.5, SV4.5; also elsewhere on the board
unnamed: SV1.4, SV2.4
OSC_L: SV3.29, SV4.29; also elsewhere on the board
RANDOM_L: SV3.30, SV4.30; also elsewhere on the board
REV_L: SV1.6, SV2.6; also elsewhere on the board
RTZ_L: SV1.10, SV2.10; also elsewhere on the board
RUN_L: SV1.12, SV2.12; also elsewhere on the board
SECTOR_0L: SV3.20, SV4.20; also elsewhere on the board
SECTOR_1L: SV3.18, SV4.18; also elsewhere on the board
SECTOR_2L: SV3.16, SV4.16; also elsewhere on the board
SECTOR_3L: SV3.14, SV4.14; also elsewhere on the board
SECTOR_4L: SV3.12, SV4.12; also elsewhere on the board
SECTOR_5L: SV3.10, SV4.10; also elsewhere on the board
SECTOR_6L: SV3.8, SV4.8; also elsewhere on the board
SECTOR_7L: SV3.6, SV4.6; also elsewhere on the board
SECTOR_8L: SV3.4, SV4.4; also elsewhere on the board
SECTOR_9L: SV3.2, SV4.2; also elsewhere on the board
SECTOR_SELECT_L: SV3.27, SV4.27; also elsewhere on the board
SEEK_INCOMPLETE_L: SV1.9, SV2.9; also elsewhere on the board
SELECT_0L: SV3.28, SV4.28; also elsewhere on the board
SELECT_1L: SV3.26, SV4.26; also elsewhere on the board
SELECT_2L: SV3.24, SV4.24; also elsewhere on the board
SELECT_3L: SV3.22, SV4.22; also elsewhere on the board
STEP_L: SV3.32, SV4.32; also elsewhere on the board
VCC: SV1.38, SV2.38; also elsewhere on the board
WRITE_H: SV3.3, SV4.3; also elsewhere on the board
WRITE_L: SV3.1, SV4.1; also elsewhere on the board

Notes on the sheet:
Interconnect Simplification

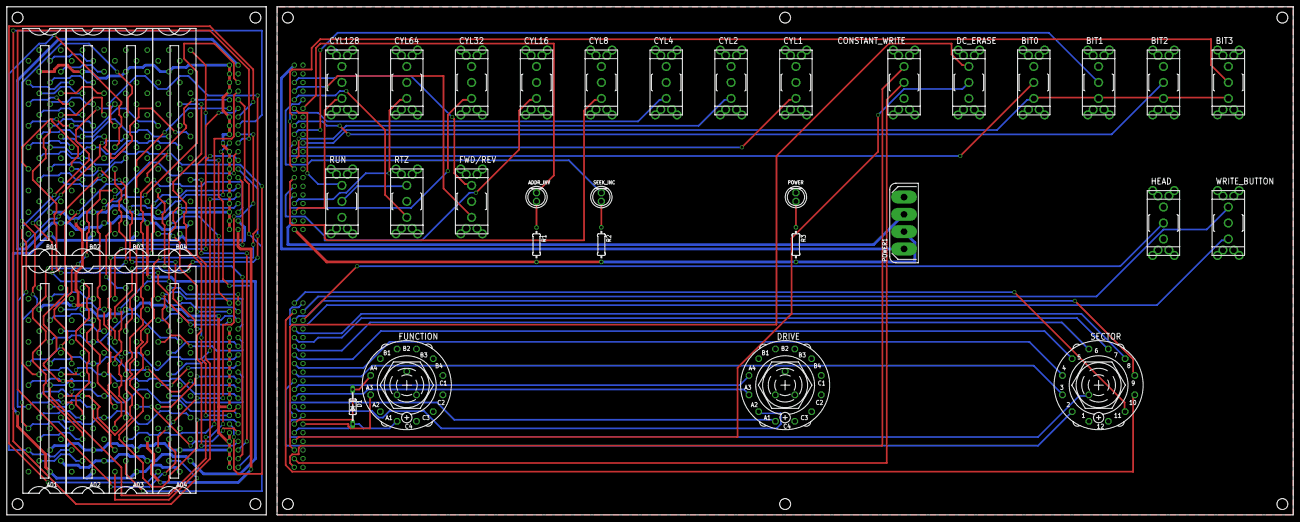
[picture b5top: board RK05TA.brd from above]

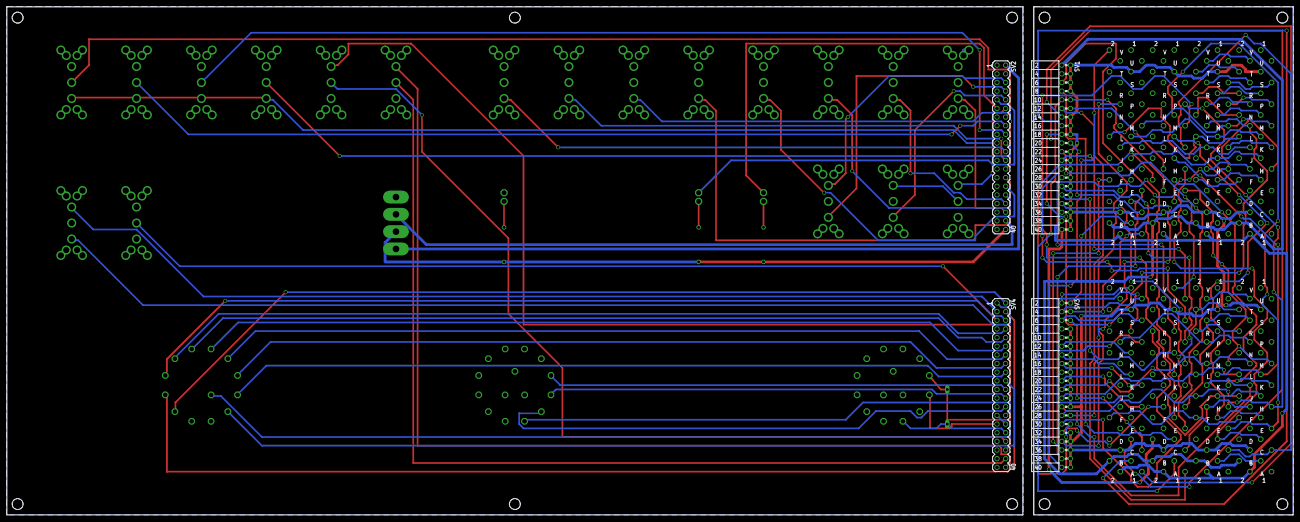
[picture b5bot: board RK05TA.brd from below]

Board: 2 copper layers, 377.8 x 149.2 mm, 42 parts (4 on the bottom side), 90 nets.
